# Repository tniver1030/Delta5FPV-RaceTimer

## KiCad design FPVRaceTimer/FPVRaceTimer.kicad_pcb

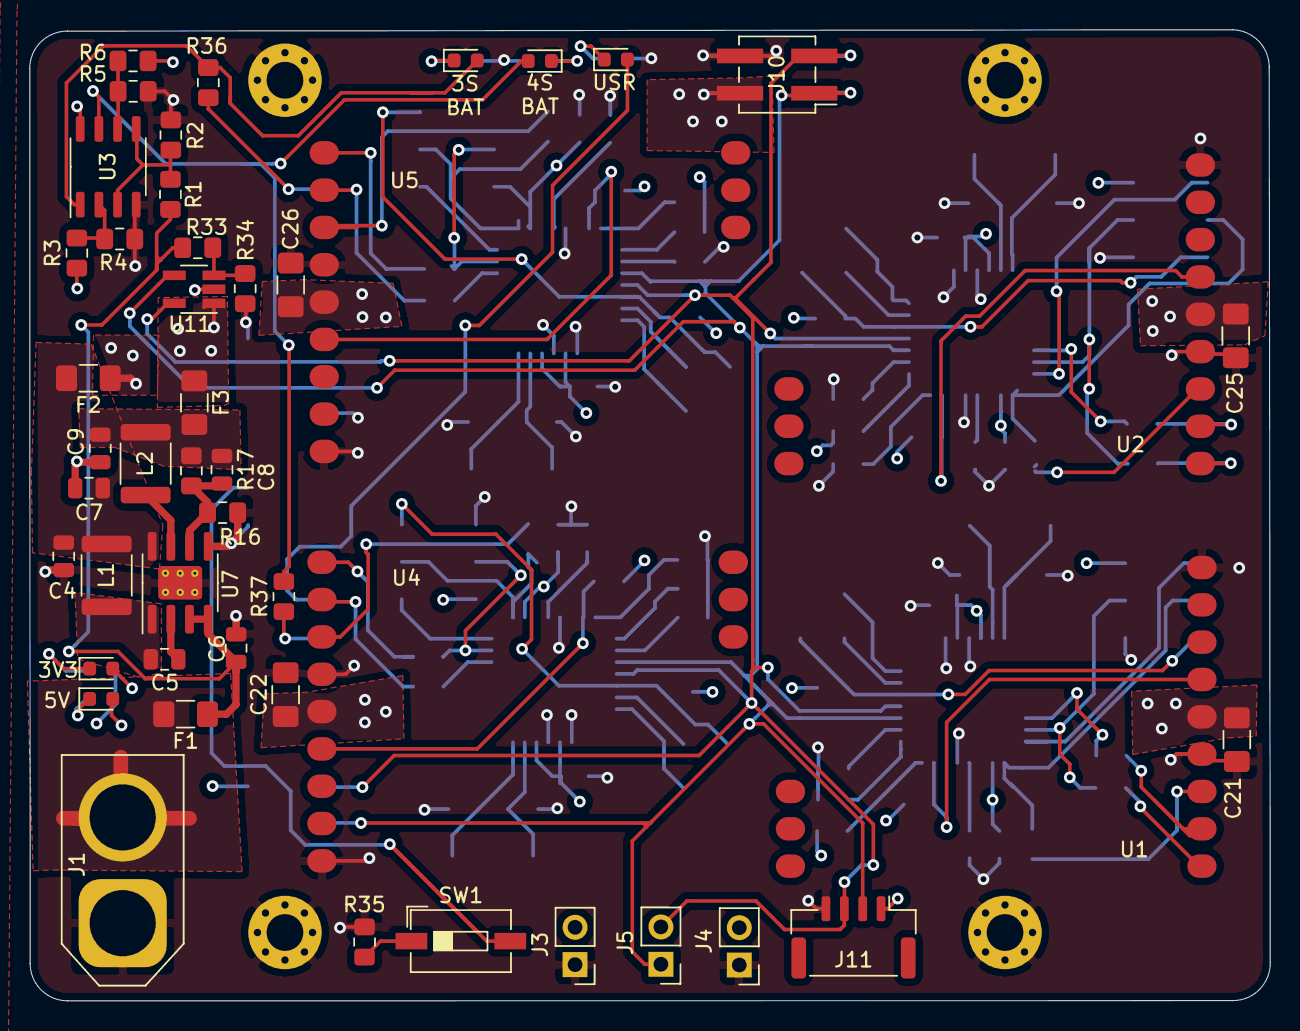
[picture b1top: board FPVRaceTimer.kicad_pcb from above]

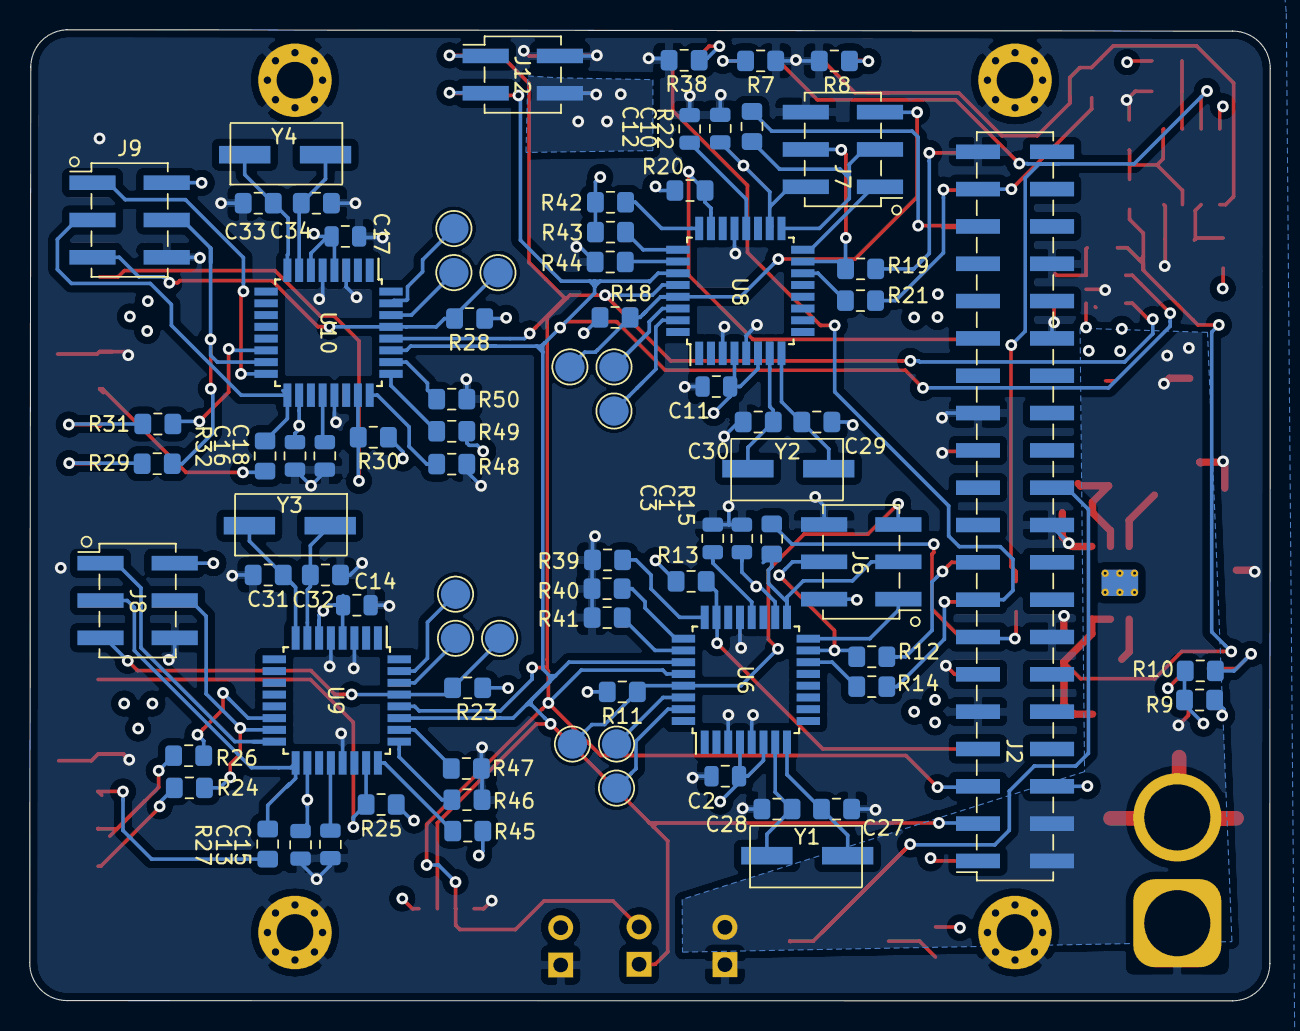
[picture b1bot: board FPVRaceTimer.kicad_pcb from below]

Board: 4 copper layers, 84.4 x 66.1 mm, 134 parts (83 on the bottom side), 97 nets.

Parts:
C1, C10, C13, C16: 1uF; C_0805_2012Metric
C2, C11, C14, C17: 4.7uF; C_0805_2012Metric
C3, C12, C15, C18: 100nF; C_0805_2012Metric
C4, C5, C6, C7, C8, C9: C; C_0805_2012Metric
C21, C22, C25, C26: C; R_1206_3216Metric_Pad1.42x1.75mm_HandSolder
C27, C28, C29, C30, C31, C32, C33, C34: C; C_0805_2012Metric_Pad1.15x1.40mm_HandSolder
D1, D2, D3, D4, D5: LED; LED_0603_1608Metric
F1, F2, F3: Fuse; Fuse_1206_3216Metric_Pad1.42x1.75mm_HandSolder
H1, H2, H3, H4: MountingHole_Pad; MountingHole_2.5mm_Pad_Via
J1: Conn_01x02; AMASS_XT60-M_1x02_P7.20mm_Vertical
J2: Raspberry_Pi_2_3; PinSocket_2x20_P2.54mm_Vertical_SMD
J3, J4, J5: Conn_01x02_Female; PinHeader_1x02_P2.54mm_Vertical
J6, J7, J8, J9: Conn_02x03_Odd_Even; PinHeader_2x03_P2.54mm_Vertical_SMD
J10, J12: Conn_02x02_Odd_Even; PinHeader_2x02_P2.54mm_Vertical_SMD
J11: Conn_01x04_Female; JST_GH_BM04B-GHS-TBT_1x04-1MP_P1.25mm_Vertical
L1, L2: INDUCTOR; L_1812_4532Metric
R1, R2, R3, R4, R5, R6, R7, R8, R9, R10, R16, R17, R35, R38: R; R_0805_2012Metric_Pad1.15x1.40mm_HandSolder
R11, R12, R14, R15, R18, R19, R21, R22, R23, R24, R26, R27, R28, R29, R31, R32: 1k; R_0805_2012Metric_Pad1.15x1.40mm_HandSolder
R13, R20, R25, R30: 100k; R_0805_2012Metric_Pad1.15x1.40mm_HandSolder
R33: 10K; R_0805_2012Metric_Pad1.15x1.40mm_HandSolder
R34: 2.2K; R_0805_2012Metric_Pad1.15x1.40mm_HandSolder
R36, R37, R39, R40, R41, R42, R43, R44, R45, R46, R47, R48, R49, R50: 10k; R_0805_2012Metric_Pad1.15x1.40mm_HandSolder
SW1: SW_DIP_x01; SW_DIP_SPSTx01_Slide_6.7x4.1mm_W6.73mm_P2.54mm_LowProfile_J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
TP1, TP2, TP3, TP4, TP5, TP6, TP7, TP8, TP9, TP10, TP11, TP12: TestPoint; TestPoint_Pad_D2.0mm
U1, U2, U4, U5: RX5808; RX5808_SMD
U3: LM393; SO-8_3.9x4.9mm_P1.27mm
U6, U8, U9, U10: ATmega328P-AU; TQFP-32_7x7mm_P0.8mm
U7: BD93291EFJ; SOIC-8-1EP_3.9x4.9mm_P1.27mm_EP2.29x3mm_ThermalVias
U11: MCP3021; SOT-23-5_HandSoldering
Y1, Y2, Y3, Y4: Crystal; CSM-3X_Crystal

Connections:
/3S_BATT_ALRM: J2.37, R36.1
/3V3: C1.1, C2.1, C10.1, C11.1, C13.1, C14.1, C16.1, C17.1, C21.1, C22.1, C25.1, C26.1, D4.2, F3.1, J4.2, J6.2, J7.2, J8.2, J9.2, J10.2, J11.1, J12.4, R3.1, R5.1, R11.2, R13.1, R18.2, R20.1, R23.2, R25.1, R28.2, R30.1, R42.2, R43.2, R45.2, R49.2, U1.5, U2.5, U3.8, U4.5, U5.5, U6.4, U6.6, U6.18, U8.4, U8.6, U8.18, U9.4, U9.6, U9.18, U10.4, U10.6, U10.18, U11.1
/4S_BATT_ALRM: J2.13, R37.1
/5V: D3.2, F2.1, J2.2, J2.4, J3.2
/BATT_SEL: J2.22, SW1.2
/MCU/ADC: R13.2, U4.4, U6.23
/MCU/CH1: R12.2, U4.9
/MCU/CH2: R14.2, U4.8
/MCU/CH3: R15.2, U4.7
/MCU/MISO: J6.1, U6.16
/MCU/MOSI: J6.4, R12.1, U6.15
/MCU/RST: J6.5, R11.1, TP9.1, U6.29
/MCU/SCK: J6.3, R15.1, U6.17
/SCL: J2.5, J5.2, J10.3, J11.3, J12.1, U6.28, U8.28, U9.28, U10.28, U11.5
/SDA: J2.3, J5.1, J10.1, J11.2, J12.3, U6.27, U8.27, U9.27, U10.27, U11.4
/USR_LED: D5.2, J2.15
/VBAT: C6.1, F1.1, R1.1, R33.2, U7.3, U7.4
/VoltageRegulation/3V3_OUT: C8.1, C9.1, F3.2, L2.1, R17.1
/VoltageRegulation/5V_OUT: C4.1, C7.1, F2.2, L1.2, U7.8
/sheet5E4ABAF5/ADC: R20.2, U5.4, U8.23
/sheet5E4ABAF5/CH1: R19.2, U5.9
/sheet5E4ABAF5/CH2: R21.2, U5.8
/sheet5E4ABAF5/CH3: R22.2, U5.7
/sheet5E4ABAF5/MISO: J7.1, U8.16
/sheet5E4ABAF5/MOSI: J7.4, R19.1, U8.15
/sheet5E4ABAF5/RST: J7.5, R18.1, TP10.1, U8.29
/sheet5E4ABAF5/SCK: J7.3, R22.1, U8.17
/sheet5E4ACBC0/ADC: R25.2, U1.4, U9.23
/sheet5E4ACBC0/CH1: R24.2, U1.9
/sheet5E4ACBC0/CH2: R26.2, U1.8
/sheet5E4ACBC0/CH3: R27.2, U1.7
/sheet5E4ACBC0/MISO: J8.1, U9.16
/sheet5E4ACBC0/MOSI: J8.4, R24.1, U9.15
/sheet5E4ACBC0/RST: J8.5, R23.1, TP11.1, U9.29
/sheet5E4ACBC0/SCK: J8.3, R27.1, U9.17
/sheet5E4ADD50/ADC: R30.2, U2.4, U10.23
/sheet5E4ADD50/CH1: R29.2, U2.9
/sheet5E4ADD50/CH2: R31.2, U2.8
/sheet5E4ADD50/CH3: R32.2, U2.7
/sheet5E4ADD50/MISO: J9.1, U10.16
/sheet5E4ADD50/MOSI: J9.4, R29.1, U10.15
/sheet5E4ADD50/RST: J9.5, R28.1, TP12.1, U10.29
/sheet5E4ADD50/SCK: J9.3, R32.1, U10.17
GND: C1.2, C2.2, C3.2, C4.2, C6.2, C7.2, C9.2, C10.2, C11.2, C12.2, C13.2, C14.2, C15.2, C16.2, C17.2, C18.2, C21.2, C22.2, C25.2, C26.2, C27.2, C28.2, C29.2, C30.2, C31.2, C32.2, C33.2, C34.2, H1.1, H2.1, H3.1, H4.1, J1.1, J2.6, J2.9, J2.14, J2.20, J2.25, J2.30, J2.34, J2.39, J3.1, J4.1, J6.6, J7.6, J8.6, J9.6, J10.4, J11.4, J12.2, R2.2, R4.2, R6.2, R7.1, R8.1, R9.1, R10.1, R16.2, R34.1, R35.2, R38.1, R39.2, R40.2, R41.2, R44.2, R46.2, R47.2, R48.2, R50.2, U1.1, U1.6, U2.1, U2.6, U3.4, U4.1, U4.6, U5.1, U5.6, U6.3, U6.5, U6.21, U7.5, U7.9, U8.3, U8.5, U8.21, U9.3, U9.5, U9.21, U10.3, U10.5, U10.21, U11.2
unnamed: C3.1, U6.20
unnamed: C5.1, L1.1, U7.1
unnamed: C5.2, U7.2
unnamed: C8.2, R16.1, R17.2, U7.6
unnamed: C12.1, U8.20
unnamed: C15.1, U9.20
unnamed: C18.1, U10.20
unnamed: C27.1, U6.8, Y1.2
unnamed: C28.1, U6.7, Y1.1
unnamed: C29.1, U8.8, Y2.2
unnamed: C30.1, U8.7, Y2.1
unnamed: C31.1, U9.8, Y3.2
unnamed: C32.1, U9.7, Y3.1
unnamed: C33.1, U10.8, Y4.2
unnamed: C34.1, U10.7, Y4.1
unnamed: D1.1, R7.2
unnamed: D1.2, R37.2, U3.7
unnamed: D2.1, R8.2
unnamed: D2.2, R36.2, U3.1
unnamed: D3.1, R9.2
unnamed: D4.1, R10.2
unnamed: D5.1, R38.2
unnamed: F1.2, J1.2
unnamed: L2.2, U7.7
unnamed: R1.2, R2.1, U3.3, U3.5
unnamed: R3.2, R4.1, U3.2
unnamed: R5.2, R6.1, U3.6
unnamed: R14.1, U6.14
unnamed: R21.1, U8.14
unnamed: R26.1, U9.14
unnamed: R31.1, U10.14
unnamed: R33.1, R34.2, U11.3
unnamed: R35.1, SW1.1
unnamed: R39.1, U6.24
unnamed: R40.1, U6.25
unnamed: R41.1, U6.26
unnamed: R42.1, U8.24
unnamed: R43.1, U8.25
unnamed: R44.1, U8.26
unnamed: R45.1, U9.24
unnamed: R46.1, U9.25
unnamed: R47.1, U9.26
unnamed: R48.1, U10.24
unnamed: R49.1, U10.25
unnamed: R50.1, U10.26
unnamed: TP1.1, U6.30
unnamed: TP2.1, U6.31
unnamed: TP3.1, U8.30
unnamed: TP4.1, U8.31
unnamed: TP5.1, U9.30
unnamed: TP6.1, U9.31
unnamed: TP7.1, U10.30
unnamed: TP8.1, U10.31

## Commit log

2020-03-22 InitCommit
